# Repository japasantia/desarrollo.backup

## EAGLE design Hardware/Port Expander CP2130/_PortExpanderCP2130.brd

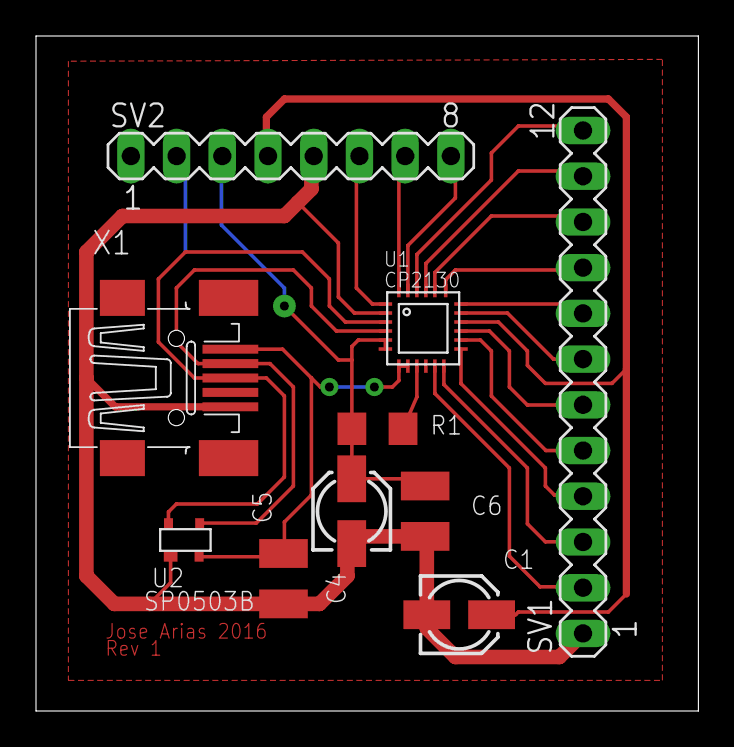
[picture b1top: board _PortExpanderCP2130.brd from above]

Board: 2 copper layers, 36.8 x 37.5 mm, 10 parts (0 on the bottom side), 21 nets.

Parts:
C1, C5: 4.7uF; 153CLV-0405
C4, C6: 0.1uF; C1210
R1: 4.7K; R1206
SV1: MA12-1
SV2: MA08-1
U1: CP2130; QFN-24
U2: SP0503B; SOT143
X1: MINI-USB-32005-201; 32005-201

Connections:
GND: C1.-, C4.2, C5.-, C6.2, SV1.1, SV2.5, U1.2, U2.1, X1.5
GPIO0: SV1.12, U1.22
GPIO1: SV1.11, U1.21
GPIO2: SV1.10, U1.20
GPIO3: SV1.9, U1.19
GPIO4: SV1.8, U1.18
GPIO5: SV1.7, U1.17
GPIO6: SV1.6, U1.15
GPIO7: SV1.5, U1.14
GPIO8: SV1.4, U1.13
GPIO9: SV1.3, U1.12
GPIO10: SV1.2, U1.11
MISO: SV2.7, U1.24
MOSI: SV2.8, U1.23
unnamed: R1.1, U1.9
SCK: SV2.6, U1.1
USB_D+: U1.3, U2.4, X1.3
USB_D-: U1.4, U2.3, X1.2
USB_VBUS: C4.1, SV2.2, U1.7, U1.8, U2.2, X1.1
VDD: C5.+, C6.1, R1.2, SV2.3, U1.5, U1.6
VPP: C1.+, SV2.4, U1.16
